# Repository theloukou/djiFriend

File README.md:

# djiFriend
Device for managing DJI Mini/Mini2 batteries

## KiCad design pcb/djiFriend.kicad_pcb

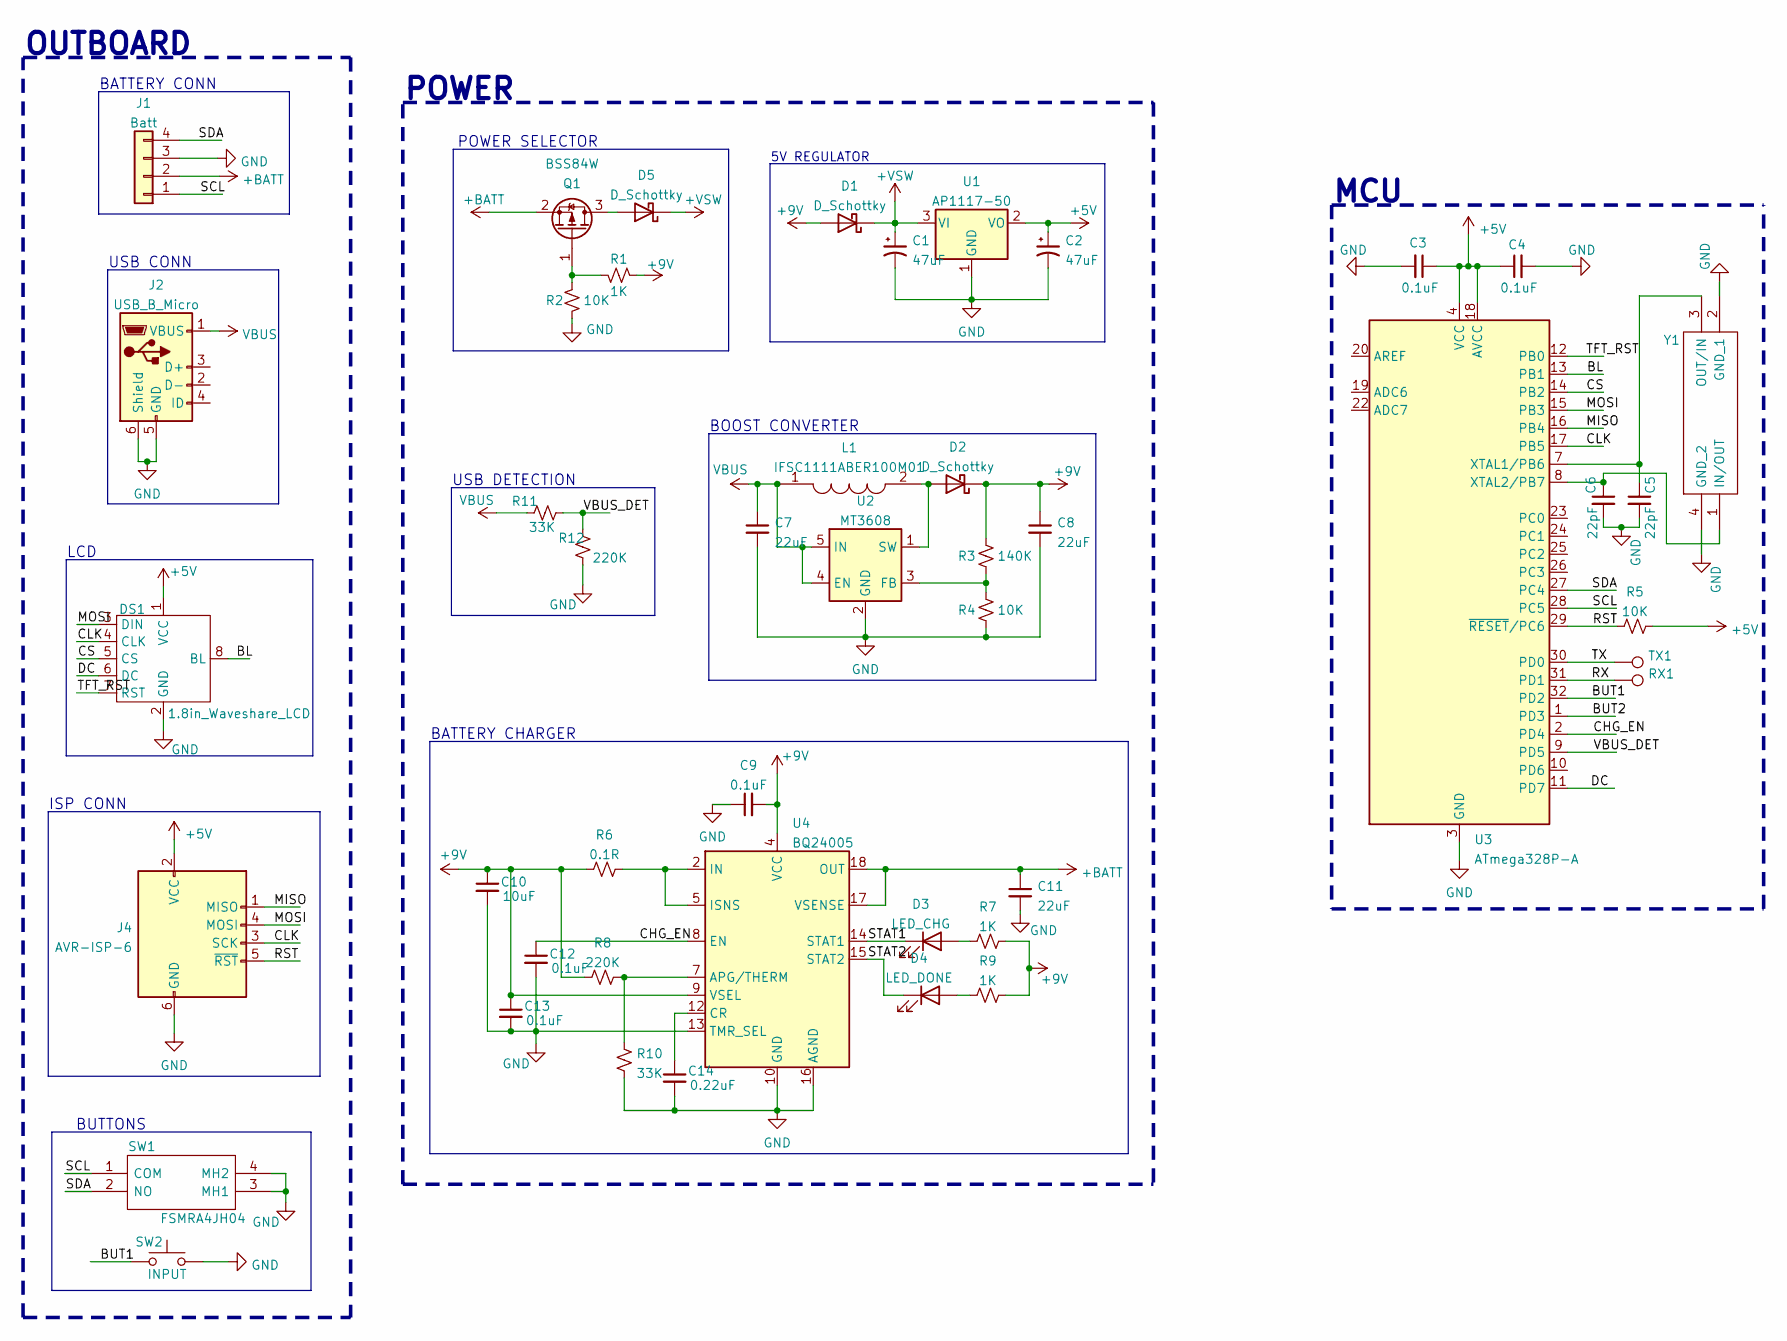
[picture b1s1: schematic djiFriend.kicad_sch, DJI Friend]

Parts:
C1, C2: 47uF; CP_Elec_6.3x5.8
C3, C4, C9, C12, C13: 0.1uF; C_0805_2012Metric_Pad1.18x1.45mm_HandSolder
C5, C6: 22pF; C_0805_2012Metric_Pad1.18x1.45mm_HandSolder
C7, C8, C11: 22uF; C_0805_2012Metric_Pad1.18x1.45mm_HandSolder
C10: 10uF; C_0805_2012Metric_Pad1.18x1.45mm_HandSolder
C14: 0.22uF; C_0805_2012Metric_Pad1.18x1.45mm_HandSolder
D1, D2, D5: D_Schottky; D_SOD-323F; Manufacturer_Part_Number PMEG2020EJF; Mouser Part Number 771-PMEG2020EJF
D3: LED_CHG; LED_D3.0mm
D4: LED_DONE; LED_D3.0mm
DS1: 1.8in_Waveshare_LCD; 1.8in Waveshare LCD
J1: Batt; JST_PH_S4B-PH-K_1x04_P2.00mm_Horizontal
J2: USB_B_Micro; USB_Micro-B_Amphenol_10118194_Horizontal; Manufacturer_Part_Number 105017-0001; Mouser Part Number 538-105017-0001
J4: AVR-ISP-6; PinHeader_2x03_P2.00mm_Vertical
L1: IFSC1111ABER100M01; Mouser Part Number 70-IFSC1111ABER100M0
Q1: BSS84W; TSOT-23; Manufacturer_Part_Number BSS84W-7-F; Mouser Part Number 621-BSS84W-F
R1: 1K; R_0805_2012Metric_Pad1.20x1.40mm_HandSolder
R2: 10K; R_0805_2012Metric_Pad1.20x1.40mm_HandSolder
R3: 140K; R_0805_2012Metric_Pad1.20x1.40mm_HandSolder
R4, R5: 10K; R_0805_2012Metric
R6: 0.1R; R_1206_3216Metric_Pad1.30x1.75mm_HandSolder; Manufacturer_Part_Number ERJ-8RSJR10V; Mouser Part Number 667-ERJ-8RSJR10V
R7, R9: 1K; R_0805_2012Metric
R8, R12: 220K; R_0805_2012Metric
R10, R11: 33K; R_0805_2012Metric
RX1: TestPoint; TestPoint_Pad_D1.5mm
SW1: FSMRA4JH04; Mouser Part Number 506-FSMRA4JH04
SW2: INPUT; SW_TH_Tactile_Omron_B3F-10xx
TX1: TestPoint; TestPoint_Pad_D1.5mm
U1: AP1117-50; SOT-223-3_TabPin2; Manufacturer_Part_Number LD1117S50TR; Mouser Part Number 511-LD1117S50
U2: MT3608; SOT-23-6
U3: ATmega328P-A; TQFP-32_7x7mm_P0.8mm
U4: BQ24005; HTSSOP-20-1EP_4.4x6.5mm_P0.65mm_EP3.4x6.5mm_Mask2.4x3.7mm; Manufacturer_Part_Number BQ24005PWPR; Mouser Part Number 595-BQ24005PWPR
Y1: ECS-160-8-33B-CTN-TR; ECS160833BCTNTR; Mouser Part Number 520-ECS160833BCTN-TR

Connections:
+5V: C2.1, C3.1, C4.1, DS1.1 (VCC), J4.2 (VCC), R5.2, U1.2 (VO), U3.4 (VCC), U3.6 (VCC), U3.18 (AVCC)
+9V: C8.1, C9.2, C10.1, C13.1, D1.2 (A), D2.1 (K), R1.2, R3.1, R6.1, R7.2, R8.2, R9.2, U4.4 (VCC), U4.9 (VSEL)
+BATT: C11.1, J1.2, Q1.2 (S), U4.17 (VSENSE), U4.18 (OUT), U4.19 (OUT)
+VSW: C1.1, D1.1 (K), D5.1 (K), U1.3 (VI)
/BL: DS1.8 (BL), U3.13 (PB1)
/BUT1: SW2.1 (A), SW2.2 (A), U3.32 (PD2)
/BUT2: U3.1 (PD3)
/CHG_EN: C12.1, U3.2 (PD4), U4.8 (EN)
/CLK: DS1.4 (CLK), J4.3 (SCK), U3.17 (PB5)
/CS: DS1.5 (CS), U3.14 (PB2)
/DC: DS1.6 (DC), U3.11 (PD7)
/MISO: J4.1 (MISO), U3.16 (PB4)
/MOSI: DS1.3 (DIN), J4.4 (MOSI), U3.15 (PB3)
/RST: J4.5 (~RST), R5.1, U3.29 (~RESET/PC6)
/RX: RX1.1, U3.31 (PD1)
/SCL: J1.1, SW1.1 (COM), U3.28 (PC5)
/SDA: J1.4, SW1.2 (NO), U3.27 (PC4)
/STAT1: D3.1 (K), U4.14 (STAT1)
/STAT2: D4.1 (K), U4.15 (STAT2)
/TFT_RST: DS1.7 (RST), U3.12 (PB0)
/TX: TX1.1, U3.30 (PD0)
/VBUS_DET: R11.2, R12.1, U3.9 (PD5)
GND: C1.2, C2.2, C3.2, C4.2, C5.2, C6.2, C7.2, C8.2, C9.1, C10.2, C11.2, C12.2, C13.2, C14.2, DS1.2 (GND), J1.3, J2.5 (GND), J2.6 (Shield), J4.6 (GND), R2.1, R4.2, R10.2, R12.2, SW1.3 (MH1), SW1.4 (MH2), SW2.3 (B), SW2.4 (B), U1.1 (GND), U2.2 (GND), U3.3 (GND), U3.5 (GND), U3.21 (GND), U4.10 (GND), U4.13 (TMR_SEL), U4.16 (AGND), U4.21 (GND), Y1.2 (GND_1), Y1.4 (GND_2)
unnamed: C5.1, U3.7 (XTAL1/PB6), Y1.3 (OUT/IN)
unnamed: C6.1, U3.8 (XTAL2/PB7), Y1.1 (IN/OUT)
unnamed: C14.1, U4.12 (CR)
unnamed: D2.2 (A), L1.2, U2.1 (SW)
unnamed: D3.2 (A), R7.1
unnamed: D4.2 (A), R9.1
unnamed: Q1.1 (G), R1.1, R2.2
unnamed: D5.2 (A), Q1.3 (D)
unnamed: R3.2, R4.1, U2.3 (FB)
unnamed: R6.2, U4.2 (IN), U4.3 (IN), U4.5 (ISNS)
unnamed: R8.1, R10.1, U4.7 (APG/THERM)
VBUS: C7.1, J2.1 (VBUS), L1.1, R11.1, U2.4 (EN), U2.5 (IN)

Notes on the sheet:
ISP CONN
BATTERY CONN
USB DETECTION
5V REGULATOR
LCD
BATTERY CHARGER
OUTBOARD
POWER SELECTOR
BOOST CONVERTER
USB CONN
POWER
BUTTONS
MCU

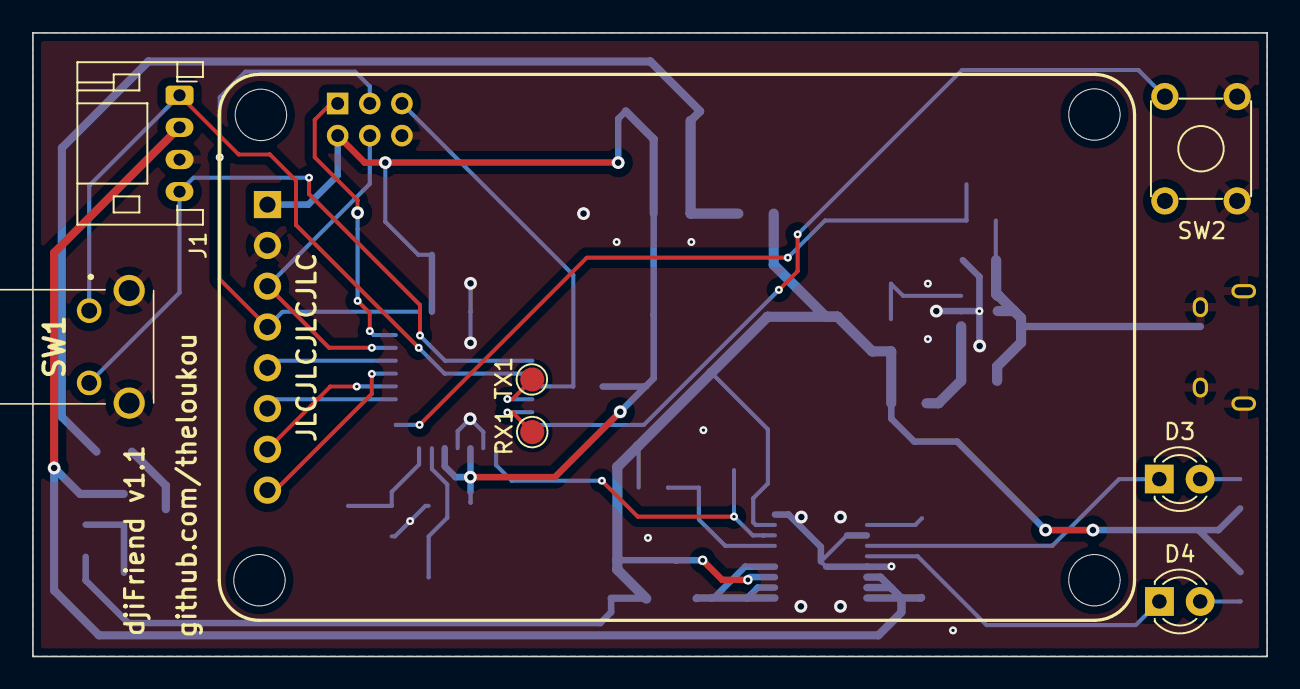
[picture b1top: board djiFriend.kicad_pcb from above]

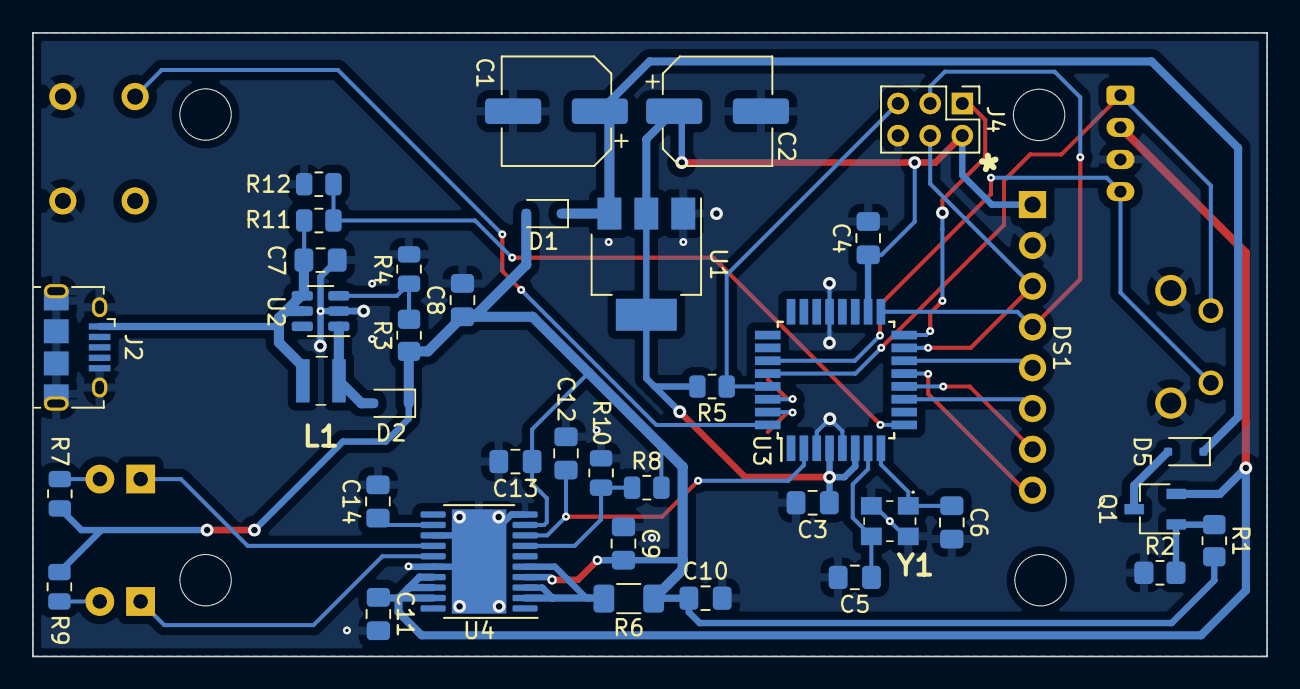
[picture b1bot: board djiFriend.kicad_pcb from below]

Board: 2 copper layers, 76.9 x 38.8 mm, 46 parts (38 on the bottom side), 34 nets.

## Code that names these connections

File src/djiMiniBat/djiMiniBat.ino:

#define NO_BAT

#define BUT1 2
#define BUT2 3
#define CHG_EN 4
#define VBUS_DET 5
#define LCD_BL 9

#include <Wire.h>
#include <SPI.h>
#include "Adafruit_GFX.h"
#include "Adafruit_ST7735.h"

Adafruit_ST7735 tft = Adafruit_ST7735(10, 7, 8);

#define BUFFER_LEN 32
uint8_t i2cBuffer[BUFFER_LEN];

bool batActive = false;
bool batActiveLast = false;
bool vbus = false;
bool charging = false;
volatile bool but1Pressed = false;

char *djiserial;
String formatted_date;
int16_t curr;
uint16_t fullChargeCap, tempK, remainCap, fullChargeTime;
uint8_t cycles, relCharge, absCharge;
double volt, cell1, cell2, tempC;

void setup() {
  Serial.begin(115200);

  pinMode(BUT1, INPUT_PULLUP);
  pinMode(BUT2, INPUT_PULLUP);
  pinMode(CHG_EN, OUTPUT);
  pinMode(VBUS_DET, INPUT);
  pinMode(LCD_BL, OUTPUT);

  attachInterrupt(digitalPinToInterrupt(BUT1), but1ISR, FALLING);
  digitalWrite(CHG_EN, LOW);
  digitalWrite(LCD_BL, HIGH);

  initLCD();

  Wire.begin();
  Wire.setClock(100000);

  delay(1500);
  clearLCD();
  delay(500);
}

void loop() {
  batActive = batPresent();
  vbus = digitalRead(VBUS_DET);

  if (!vbus || !batActive) {
    stopCharging();
  }
  else if (vbus && batActive) {
    if (but1Pressed) {
      but1Pressed = false;
      if (!charging) {
        startCharging();
      }
      else if (charging) {
        stopCharging();
      }
    }
  }

  if (batActive) {
    if (batActive != batActiveLast) {
      getStaticBatData();
      clearLCD();
      delay(100);
    }
    getDynamicBatData();
    updateLCD();
  }
  else {
    updateLCDnoBat();
  }
  printBatData();
  batActiveLast = batActive;

  delay(1000);
}

void but1ISR() {
  but1Pressed = true;
}

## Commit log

2022-10-17 1st commit
2022-10-17 added gerbers, updated version numbers
2022-11-20 Updates to code, mior adjustments to pcb
